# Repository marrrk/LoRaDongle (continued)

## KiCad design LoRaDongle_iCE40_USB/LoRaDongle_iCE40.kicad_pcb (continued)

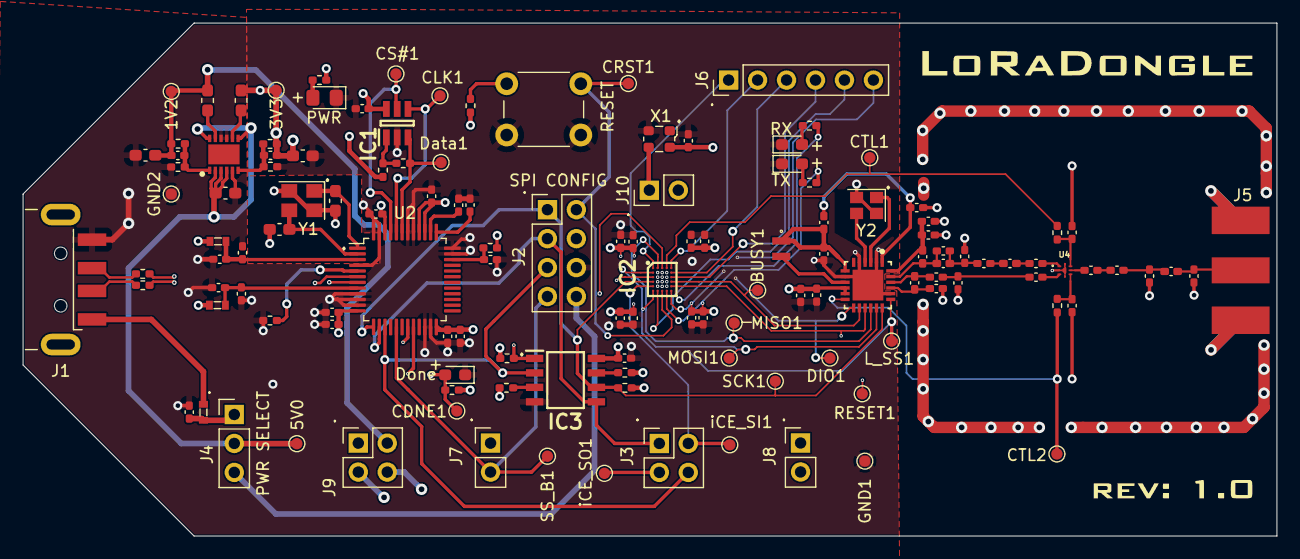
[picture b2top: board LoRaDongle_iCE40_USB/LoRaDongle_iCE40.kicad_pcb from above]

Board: 4 copper layers, 110.0 x 45.0 mm, 135 parts (1 on the bottom side), 83 nets.

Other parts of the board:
G1: LOGO; LoRaDongleLogo
G2: LOGO; rev1.0
G3: LOGO; mark_njoroge
RESET: SW_Push; SW_PUSH_6mm_H5mm

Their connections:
/ICE_CRESET: RESET.1; also elsewhere on the board
GND: RESET.2; also elsewhere on the board

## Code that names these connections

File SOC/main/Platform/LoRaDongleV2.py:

from litex.build.generic_platform import *
from litex.build.lattice import LatticePlatform
from litex.build.lattice.programmer import IceStormProgrammer


# IOs--------------------------------------------------------------------------------

_io = [
    # Clk
    ("clk", 0, Pins("46"), IOStandard("LVCMOS33")),
    #("cpu_reset", 0, Pins("21"), IOStandard("LVCMOS33")),

    ("btn", 0, Pins("21"), IOStandard("LVCMOS33")),     #Testing Input Button for interrupt!


    # Leds
    ("user_led", 0, Pins("37"),  IOStandard("LVCMOS33")),           #RX LED
    ("user_led", 1, Pins("36"),  IOStandard("LVCMOS33")),           #TX LED


    #### When changing config pins, make sure to change the firmware as well. sx126x_hal.c and Radio.c uses these pins to set up radio
    #LoRa Configuration Pins
    ("lora_config", 0, Pins("35"), IOStandard("LVCMOS33")),           #ANT_SW, Output
    ("lora_config", 1, Pins("31"), IOStandard("LVCMOS33")),           #RESET, Output

    #Dio Interrupt Pin
    ("dio1", 0, Pins("34"), IOStandard("LVCMOS33")),          #DIO1, Input


    #BusyPin
    ("lora_busy", 0, Pins("32"), IOStandard("LVCMOS33")),          #Busy, Input
    

    #UART
    ("serial", 0,
        Subsignal("tx", Pins("9")),
        Subsignal("rx", Pins("6")),
        IOStandard("LVCMOS33"),
    ),

    #SPIFlash
    ("spiflash", 0,
        Subsignal("cs_n", Pins("16"), IOStandard("LVCMOS33")),
        Subsignal("clk",  Pins("15"), IOStandard("LVCMOS33")),
        Subsignal("miso", Pins("17"), IOStandard("LVCMOS33")),
        Subsignal("mosi", Pins("14"), IOStandard("LVCMOS33")),
    ),


    #SPI
    ("spi_bus",0,                   
        Subsignal("clk", Pins("26")),                  
        Subsignal("cs_n", Pins("25")),                 
        Subsignal("mosi", Pins("27")),                 
        Subsignal("miso", Pins("28")),                 
        IOStandard("LVCMOS33"),
    ),


    #I2C
    ("i2c_bus",0,
        Subsignal("sda", Pins("18")),
        Subsignal("scl", Pins("19")),
        IOStandard("LVCMOS33")
    )

]



# Platform-----------------------------------------------------------------------------

class Platform(LatticePlatform):
	default_clk_name   = "clk"
	default_clk_period = 1e9/50e6

	def __init__(self, toolchain="icestorm"):
		LatticePlatform.__init__(self, "ice40-up5k-sg48", _io, toolchain=toolchain)

	def create_programmer(self):
        	return IceStormProgrammer()

	def do_finalize(self, fragment):
		LatticePlatform.do_finalize(self, fragment)
		self.add_period_constraint(self.lookup_request("clk", loose=True), 1e9/50e6)

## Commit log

2021-09-14 added regulators
2021-09-22 fpga power circuitry
2021-09-22 updated circuitry
2021-09-22 added sx1262 library part being used
2021-09-30 adding usb interface
2021-09-30 add eeprom
2021-10-01 ft232h completed
2021-10-04 added flash memory configuration
2021-10-07 updated RF circuitry
2021-10-13 updated with dip switch
2021-11-23 Lattice fork
2021-11-23 renaming Xilinx folder
2021-12-08 initial changes to iCE40UP5k
2021-12-10 changed to sx1261
2021-12-12 connected FPGA to SX1261
2021-12-14 added footprints
2021-12-20 PCB Layout V01
2021-12-27 first traces laid
2022-01-01 added more traces
2022-01-03 breakout of bga part
2022-01-04 added to other traces
2022-01-07 added copper pours
2022-01-10 updating unconnected traces
2022-01-11 updating symbol details
2022-01-17 updated BOM
2022-01-18 switched relative libraries
2022-01-18 update footprint libary
2022-01-18 generate raw bom csv from kicad
2022-01-19 update vias and text on schematic
2022-01-27 added usb flash testpoints & jumper for fpga oscillator
2022-02-04 updating silkscreen
2022-02-06 completed silkscreen
2022-02-07 gerbers and centroid file added
2022-02-15 updating text in schematic
2022-03-08 updated submodules for xilinx
2022-05-12 minor updates to silkscreen and manufacturing images
2022-05-12 pcb files in pcb directory
2022-05-12 added soc directory and files for arty test
2022-05-18 added timers
2022-05-23 tested out spi registers
2022-05-25 minor soc update - order of pads for SPIMaster
2022-05-26 plans to test i2c
2022-05-26 tested delays between register writes of SPI
2022-05-27 sending byte on spi
2022-05-30 changed structure project, creating src, ld and .obj directory
2022-05-30 moved loopback test to spi.c
2022-06-01 added console service
2022-06-02 SOC for LoRaDongle development begins
2022-06-03 updated SoC, tested firmware, not working
2022-06-06 added flickering LED Test
2022-06-06 added flashing functionality to LoRaDOngle.py and updated platform and test code
2022-06-07 Initial Github Pages site
2022-06-07 changing github pages gem
2022-06-07 updated _config.yml
2022-06-07 bare metal content for site to test setup
2022-06-08 added a getting started
2022-06-09 add nexys A7 support for testing
2022-06-09 updated getting started
2022-06-22 brought in sx12x drivers
2022-06-24 updated spi transfer to multiple bytes at 8MHz
2022-06-28 updated spi_hal
2022-06-28 separated nexys and arty files
2022-06-28 deleted __pycache__
2022-07-04 updated sx1261 interfacing code
2022-07-06 bare metal transmit appears to be working
2022-07-15 updated ftdi and flash chip, removed xilinx project
2022-07-18 updated jumpers, connectors and testpoints
2022-07-20 updated layout and routing
2022-07-22 updated routing
2022-07-22 removed unnecessary microvias
2022-07-22 updated schematic to QFN ice40
2022-07-26 routing complete
2022-07-27 updated silkscreen
2022-08-02 updated to get receive working
2022-08-02 updated LoRaDongle code to working implementation of led flicker test
2022-08-09 removing nexys directory from main
2022-08-09 removed arty_test from main
2022-08-09 create arty_test branch
2022-08-09 updated image in getting started/programming_SOC.md
2022-08-09 updated gems
2022-08-11 moved firmware to project root
2022-08-15 changed structure of project, put realted files in same directory
2022-08-15 including gitignore
2022-08-15 updated submodule
2022-08-15 updated readmes
2022-08-15 made readme visible in SOC/
2022-08-15 ignored/deleted redundant PCB files
2022-08-15 added pcb and firmware readmes
2022-08-16 restructured firmware to have radio functions out of main.c
2022-08-16 build
2022-08-17 updated docs
2022-08-17 updated firmware readme
2022-08-19 updated manufacturing docs
2022-08-23 moved firmware into demo directory
2022-08-29 setting validate all codebase to false
2022-08-29 updated docs, main readme
2022-08-29 fixed linting issues
2022-08-30 porting to revision 2.0 of board
2022-09-01 added license
2022-09-01 update of platform file and docs
2022-09-02 updating demo firmware for testing
2022-09-06 updated default cpu and added i2c core
2022-09-06 udpdated radio testing
2022-09-19 started working on incorporating interrupts
2022-09-20 button test interrupt isr implemented
2022-09-21 added timer1 with interrupt
2022-09-26 attached interrupt to SX1261 DIO1 line
2022-09-27 updated irq
2022-09-28 separated rx and tx and demo programs
2022-10-03 updated interrupt testing, able to get rx to constantly throw interrupts
2022-10-05 cleaned up soc demo
2022-10-05 set up automatic build when running builder script
2022-10-11 implemented basic receive state machine
2022-10-11 updating tx testing
2022-10-17 updated ping pong testing, getting timer discrepencies
2022-11-03 basic tx state machine implemented
2022-11-03 removed flash function -- unused
2022-11-04 timer1 working
2022-11-07 updated code to improve planned testing functionality
2022-11-09 updated testing code
2022-11-14 updated ping pong test
2022-11-15 updated directory to working implementation of ping pong test
2022-11-18 started on testing script
2022-11-21 exploratory tests done
2022-11-23 updated testing firmware so doesn't hang when a packet is receied incorrectly
2022-11-23 updated tests
2022-12-02 updated logger script
2022-12-02 cleaned up logging script
2022-12-02 renaming test directory
2022-12-02 updated .gitignore
2022-12-02 started on analysis script
2022-12-02 updated script
2022-12-03 done structured latency testing
2022-12-04 indoor vertical tests
2022-12-06 updated analysis
2022-12-08 added more testing
2022-12-11 line of sight testing done
2022-12-12 updated floor 1 success rate
2022-12-13 redid some outdoor tests
2022-12-22 updated analyser script
2022-12-27 updated testing analysis
2023-01-02 consolidated success rates of indoor testing
2023-01-10 added some more testing
2023-01-14 updated latency tests
2023-01-21 updated cbd tests, analyser notebook
2023-02-06 updated analyser
2023-02-06 updating testing information
2023-02-07 updated test firmware
